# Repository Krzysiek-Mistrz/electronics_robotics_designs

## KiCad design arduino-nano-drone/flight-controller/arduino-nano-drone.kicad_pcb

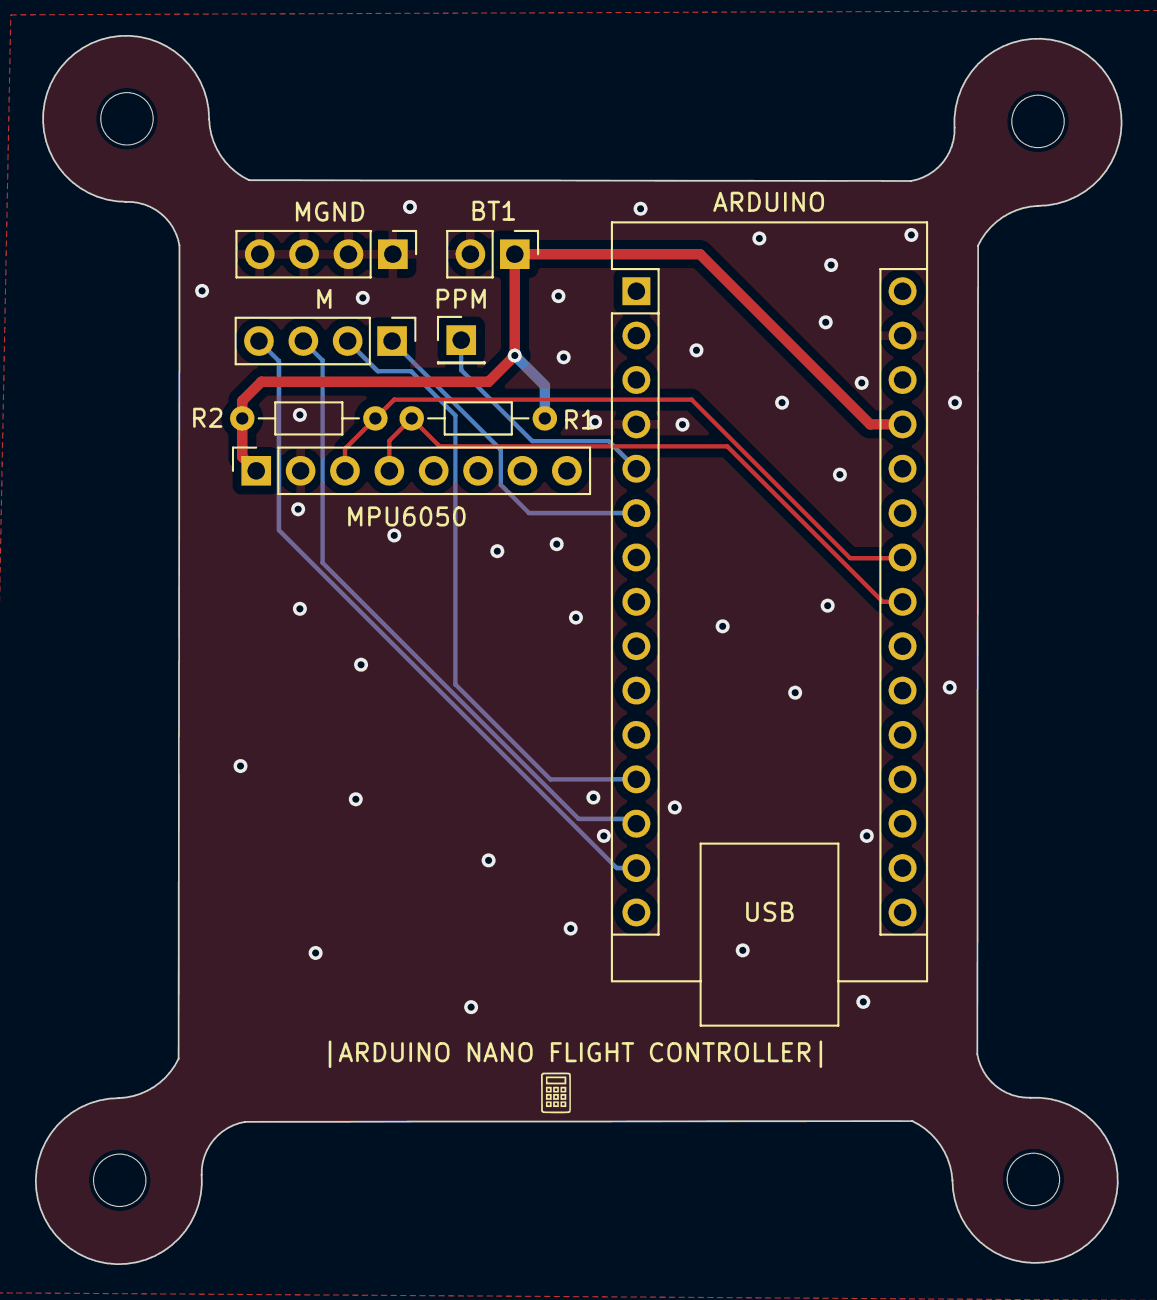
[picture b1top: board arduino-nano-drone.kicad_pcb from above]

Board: 2 copper layers, 62.2 x 70.3 mm, 8 parts (0 on the bottom side), 9 nets.

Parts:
ARDUINO: Arduino_Nano_v2.x; Arduino_Nano
BT1: Battery; PinHeader_1x02_P2.54mm_Vertical
M: Conn_01x04_Pin; PinHeader_1x04_P2.54mm_Vertical
MGND: motors pins; PinHeader_1x04_P2.54mm_Vertical
MPU6050: mpu6050 socket pins; PinSocket_1x08_P2.54mm_Vertical
PPM: Conn_01x01_Pin; PinHeader_1x01_P2.54mm_Vertical
R1, R2: 4.7k; R_Axial_DIN0204_L3.6mm_D1.6mm_P7.62mm_Horizontal

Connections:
/SCL: ARDUINO.24 (A5), MPU6050.3, R2.2
/SDA: ARDUINO.23 (A4), MPU6050.4, R1.2
GND: ARDUINO.4 (GND), ARDUINO.29 (GND), BT1.2 (-), MGND.1, MGND.2, MGND.3, MGND.4, MPU6050.2
unnamed: ARDUINO.5 (D2), PPM.1
unnamed: ARDUINO.6 (D3), M.1
unnamed: ARDUINO.12 (D9), M.2
unnamed: ARDUINO.13 (D10), M.3
unnamed: ARDUINO.14 (D11), M.4
VCC: ARDUINO.27 (+5V), BT1.1 (+), MPU6050.1, R1.1, R2.1

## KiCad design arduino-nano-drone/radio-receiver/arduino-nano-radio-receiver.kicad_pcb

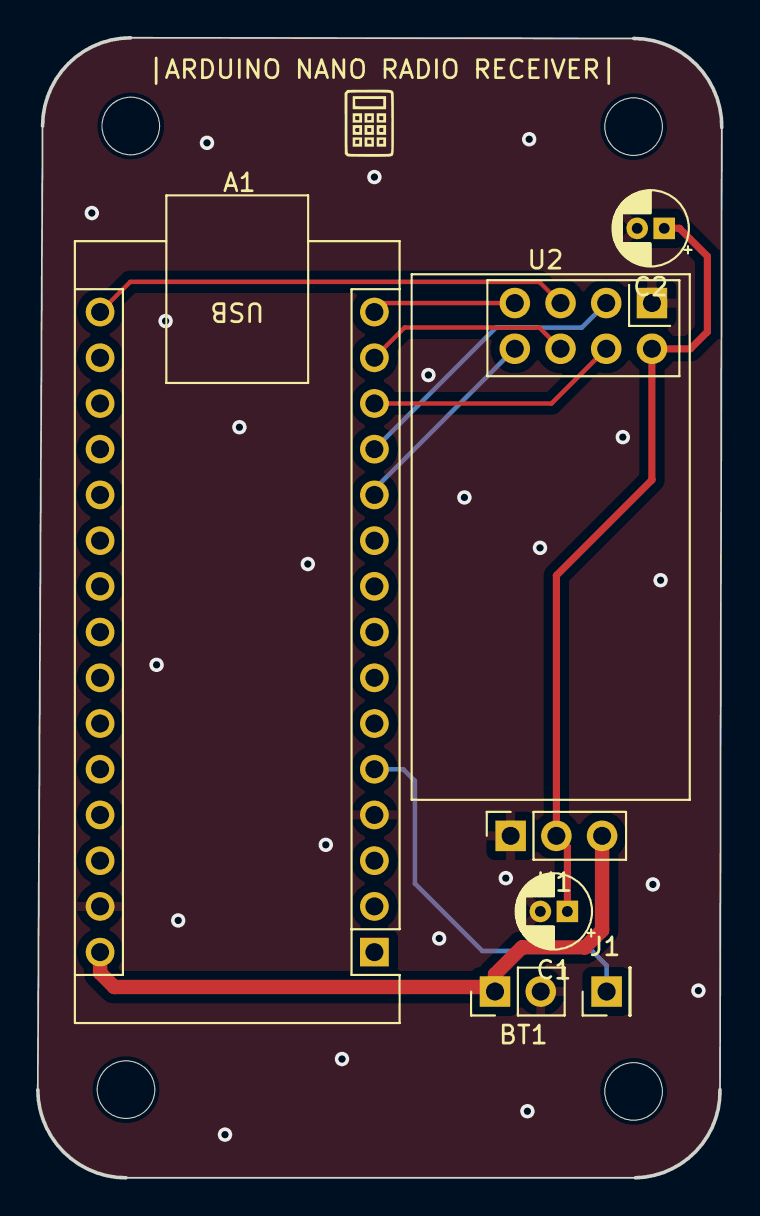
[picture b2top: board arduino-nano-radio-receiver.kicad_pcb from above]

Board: 2 copper layers, 38.0 x 63.3 mm, 7 parts (0 on the bottom side), 10 nets.

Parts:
A1: Arduino_Nano_v2.x; Arduino_Nano
BT1: Battery; PinHeader_1x02_P2.54mm_Vertical
C1, C2: 10u; CP_Radial_D4.0mm_P1.50mm
J1: Conn_01x01_Pin; PinHeader_1x01_P2.54mm_Vertical
U1: AMS1117-3.3; PinSocket_1x03_P2.54mm_Vertical
U2: NRF24L01_Breakout; nRF24L01_Breakout

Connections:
+3.3V: C1.1, C2.1, U1.2 (VO), U2.2 (VCC)
+12V: A1.30 (VIN), BT1.1 (+), U1.3 (VI)
/CE: A1.12 (D9), U2.3 (CE)
/CSN: A1.13 (D10), U2.4 (~CSN)
/IRQ: A1.11 (D8), U2.8 (IRQ)
/MISO: A1.15 (D12), U2.7 (MISO)
/MOSI: A1.14 (D11), U2.6 (MOSI)
/SCK: A1.16 (D13), U2.5 (SCK)
GND: A1.4 (GND), A1.29 (GND), BT1.2 (-), C1.2, C2.2, U1.1 (GND), U2.1 (GND)
unnamed: A1.5 (D2), J1.1

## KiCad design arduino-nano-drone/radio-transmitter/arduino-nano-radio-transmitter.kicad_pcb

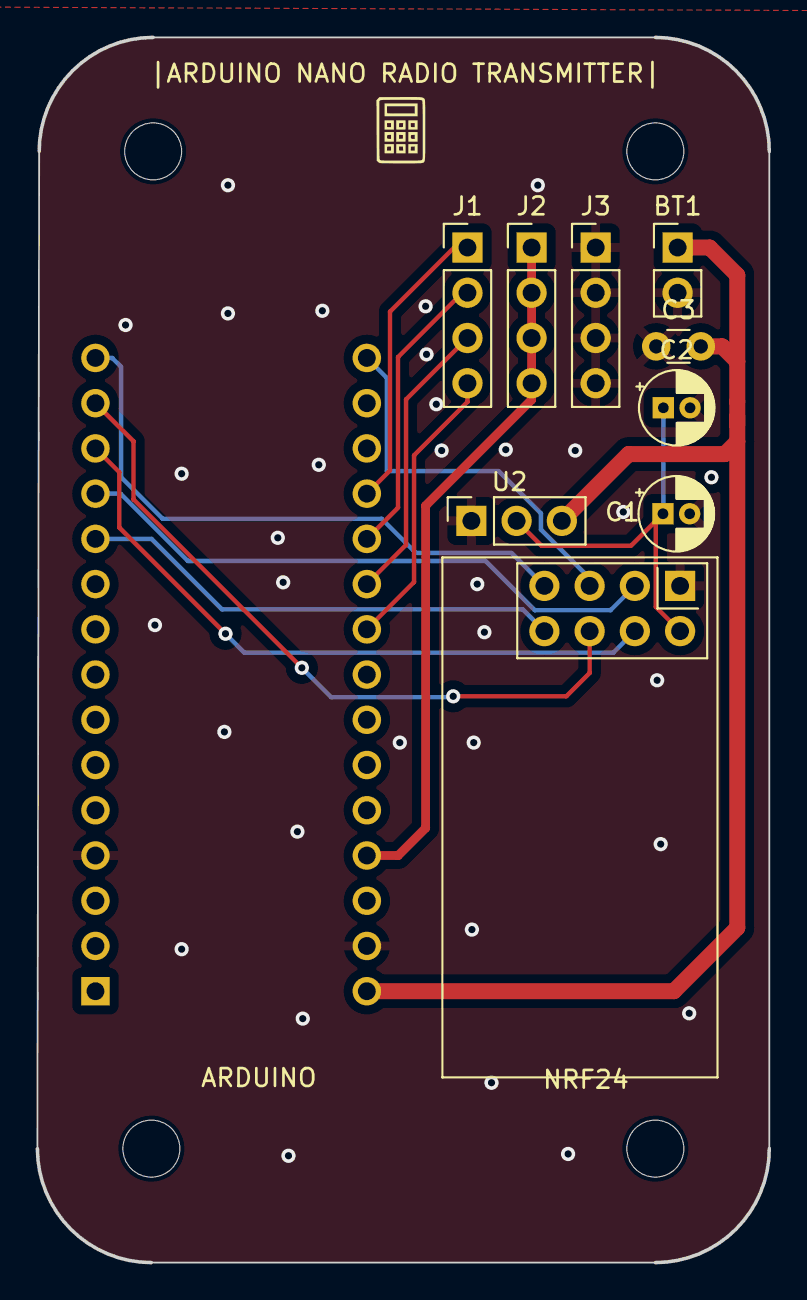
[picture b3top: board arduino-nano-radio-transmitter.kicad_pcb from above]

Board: 2 copper layers, 41.1 x 68.8 mm, 10 parts (1 on the bottom side), 14 nets.

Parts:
A1: Arduino_Nano_v2.x; Arduino_Nano
BT1: Battery; PinHeader_1x02_P2.54mm_Vertical
C1, C2: 10u; CP_Radial_D4.0mm_P1.50mm
C3: 100n; C_Disc_D3.0mm_W1.6mm_P2.50mm
J1, J2, J3: Conn_01x04_Pin; PinHeader_1x04_P2.54mm_Vertical
U2: AMS1117-3.3; PinSocket_1x03_P2.54mm_Vertical
U3: NRF24L01_Breakout; nRF24L01_Breakout

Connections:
+3.3V: C1.1, C2.1, U2.2 (VO), U3.2 (VCC)
+12V: A1.30 (VIN), BT1.1 (+), C3.2, U2.3 (VI)
/CE: A1.12 (D9), U3.3 (CE)
/CSN: A1.13 (D10), U3.4 (~CSN)
/IRQ: A1.11 (D8), U3.8 (IRQ)
/MISO: A1.15 (D12), U3.7 (MISO)
/MOSI: A1.14 (D11), U3.6 (MOSI)
/SCK: A1.16 (D13), U3.5 (SCK)
GND: A1.4 (GND), A1.29 (GND), BT1.2 (-), C1.2, C2.2, C3.1, J3.1, J3.2, J3.3, J3.4, U2.1 (GND), U3.1 (GND)
unnamed: A1.27 (+5V), J2.1, J2.2, J2.3, J2.4
unnamed: A1.19 (A0), J1.1
unnamed: A1.20 (A1), J1.2
unnamed: A1.21 (A2), J1.3
unnamed: A1.22 (A3), J1.4

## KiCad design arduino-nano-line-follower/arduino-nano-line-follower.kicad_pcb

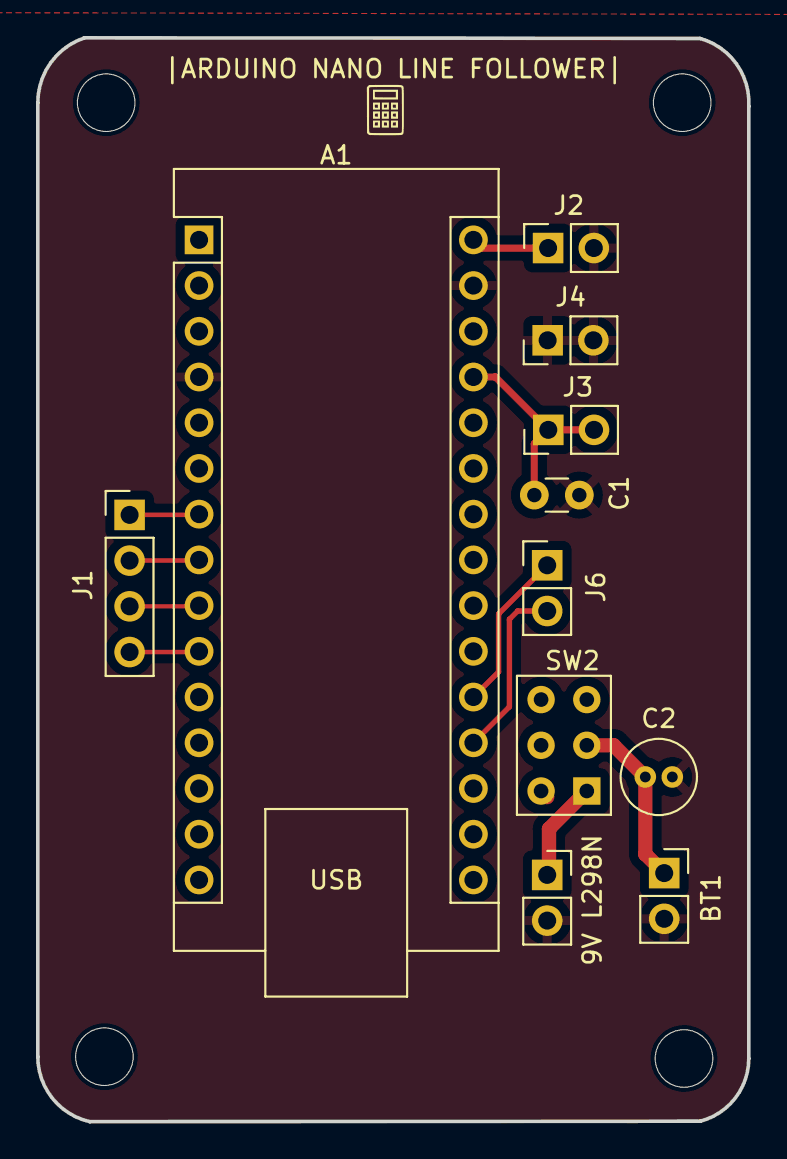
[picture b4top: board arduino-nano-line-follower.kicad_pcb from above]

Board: 2 copper layers, 39.5 x 60.2 mm, 11 parts (0 on the bottom side), 11 nets.

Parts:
9V L298N: 9v_gnd_l293d; PinSocket_1x02_P2.54mm_Vertical
A1: Arduino_Nano_Every; Arduino_Nano
BT1: Battery; PinSocket_1x02_P2.54mm_Vertical
C1: 100n; C_Disc_D3.0mm_W1.6mm_P2.50mm
C2: 10u; C_Radial_D4.0mm_H5.0mm_P1.50mm
J1: l298_input_pins; PinHeader_1x04_P2.54mm_Vertical
J2: arduino_vcc_gnd; PinSocket_1x02_P2.54mm_Vertical
J3: 5v_ir_sensors_pins; PinHeader_1x02_P2.54mm_Vertical
J4: gnd_ir_sensors_pins; PinHeader_1x02_P2.54mm_Vertical
J6: ir_signal; PinHeader_1x02_P2.54mm_Vertical
SW2: pwr_switch; SW_NKK_G1xJP

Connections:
+5V: A1.30 (VIN), J2.1
+9V: BT1.1 (+), C2.1, SW2.2
GND: 9V L298N.2, A1.4 (GND), A1.29 (GND), BT1.2 (-), C1.2, C2.2, J2.2, J4.1, J4.2
unnamed: A1.27 (+5V), C1.1, J3.1, J3.2
unnamed: A1.19 (A0), J6.2
unnamed: A1.20 (A1), J6.1
unnamed: A1.7 (D4), J1.1
unnamed: A1.8 (D5), J1.2
unnamed: A1.9 (D6), J1.3
unnamed: A1.10 (D7), J1.4
unnamed: 9V L298N.1, SW2.1

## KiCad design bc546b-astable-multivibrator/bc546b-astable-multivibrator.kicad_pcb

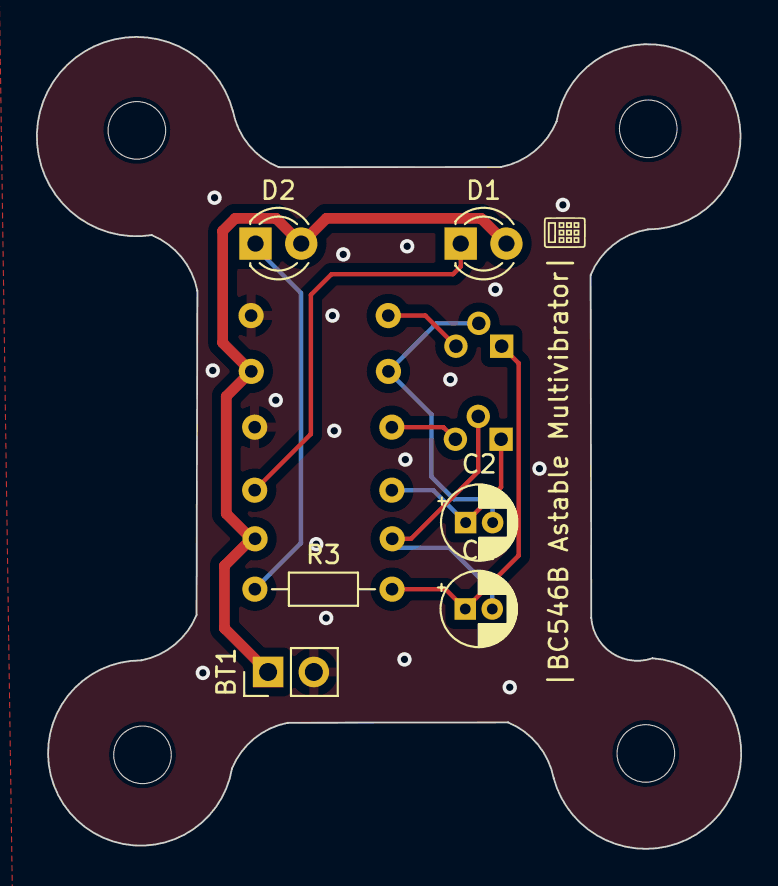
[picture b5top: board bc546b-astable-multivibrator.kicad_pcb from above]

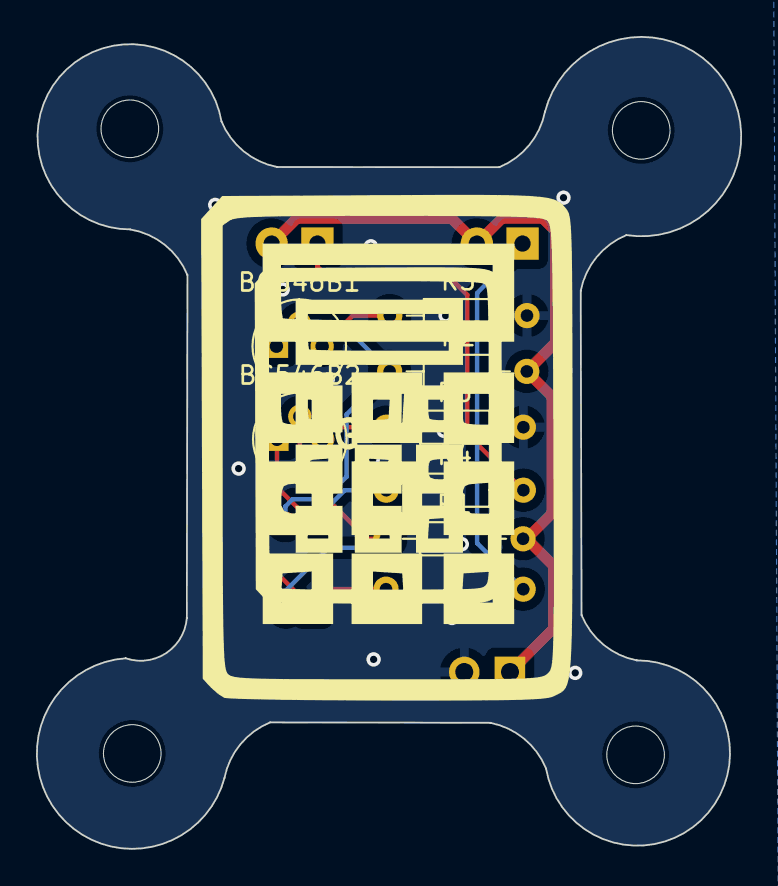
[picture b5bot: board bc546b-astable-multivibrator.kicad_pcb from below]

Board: 2 copper layers, 39.1 x 45.1 mm, 13 parts (7 on the bottom side), 10 nets.

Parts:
BC546B1, BC546B2: NPN; TO-92
BT1: Battery; PinHeader_1x02_P2.54mm_Vertical
C1, C2: 10u; CP_Radial_D4.0mm_P1.50mm
D1, D2: LED; LED_D3.0mm
R1, R2: 100k; R_Axial_DIN0204_L3.6mm_D1.6mm_P7.62mm_Horizontal
R3, R4: 560; R_Axial_DIN0204_L3.6mm_D1.6mm_P7.62mm_Horizontal
R5, R6: 100; R_Axial_DIN0204_L3.6mm_D1.6mm_P7.62mm_Horizontal

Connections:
+9V: BT1.1 (+), D1.2 (A), D2.2 (A), R1.2, R2.2
/I1: BC546B2.2 (B), C1.2, R1.1
/I2: BC546B1.2 (B), C2.2, R2.1
GND: BT1.2 (-), R5.2, R6.2
unnamed: BC546B1.1 (C), C1.1, R3.2
unnamed: BC546B1.3 (E), R5.1
unnamed: BC546B2.1 (C), C2.1, R4.1
unnamed: BC546B2.3 (E), R6.1
unnamed: D1.1 (K), R4.2
unnamed: D2.1 (K), R3.1

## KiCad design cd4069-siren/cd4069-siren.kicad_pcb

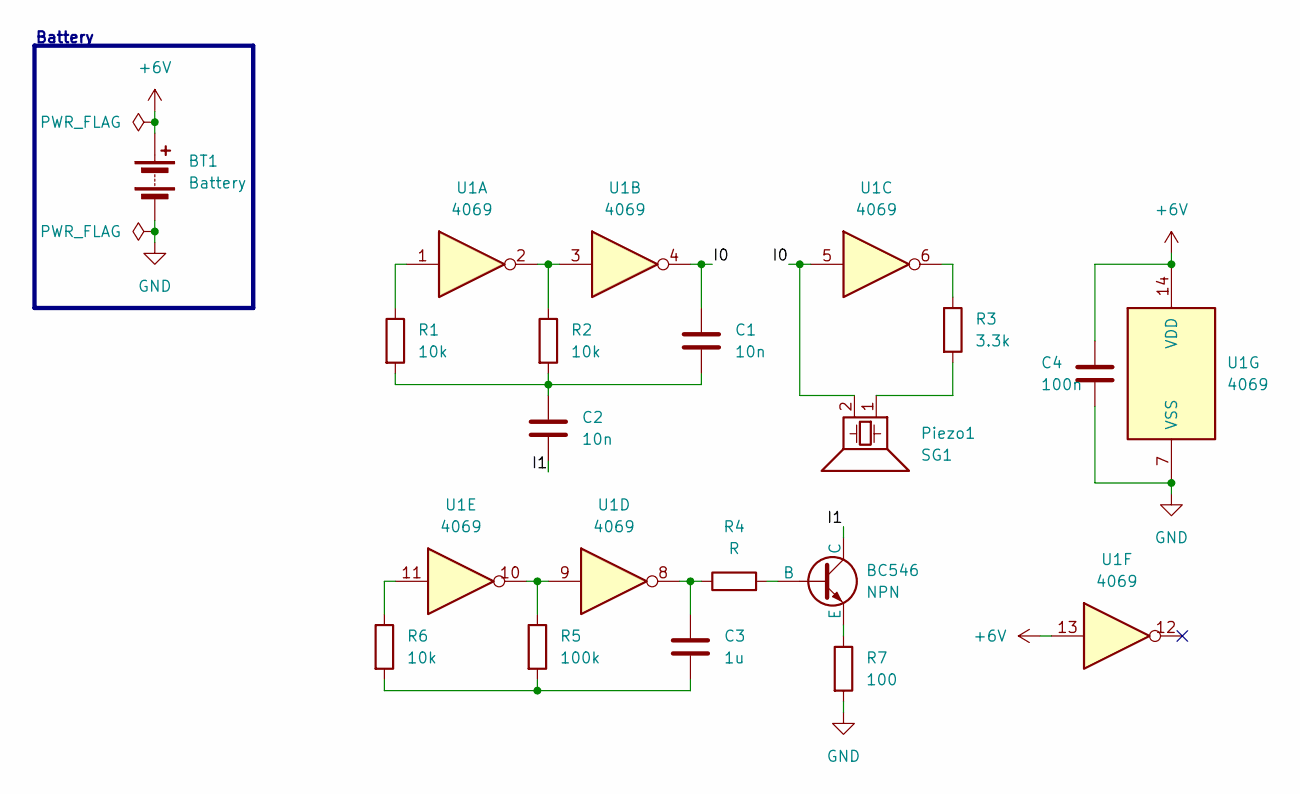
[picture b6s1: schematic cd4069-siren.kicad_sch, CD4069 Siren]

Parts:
BC546: NPN; TO-92
BT1: Battery; PinHeader_1x02_P2.54mm_Vertical
C1, C2: 10n; C_Disc_D3.0mm_W1.6mm_P2.50mm
C3: 1u; C_Disc_D3.0mm_W1.6mm_P2.50mm
C4: 100n; C_Disc_D3.0mm_W1.6mm_P2.50mm
Piezo1: SG1; Buzzer_12x9.5RM7.6
R1, R2, R6: 10k; R_Axial_DIN0204_L3.6mm_D1.6mm_P7.62mm_Horizontal
R3: 3.3k; R_Axial_DIN0204_L3.6mm_D1.6mm_P7.62mm_Horizontal
R4: R; R_Axial_DIN0204_L3.6mm_D1.6mm_P7.62mm_Horizontal
R5: 100k; R_Axial_DIN0204_L3.6mm_D1.6mm_P7.62mm_Horizontal
R7: 100; R_Axial_DIN0204_L3.6mm_D1.6mm_P7.62mm_Horizontal
U1: 4069; DIP-14_W7.62mm

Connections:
+6V: BT1.1 (+), C4.1, U1.13, U1.14 (VDD); also elsewhere on the board
/I0: C1.1, Piezo1.2, U1.4, U1.5; also elsewhere on the board
/I1: BC546.1 (C), C2.2
GND: BT1.2 (-), C4.2, R7.2, U1.7 (VSS); also elsewhere on the board
unnamed: BC546.2 (B), R4.2
unnamed: BC546.3 (E), R7.1
unnamed: C1.2, C2.1, R1.2, R2.2
unnamed 7: C3.1, R4.1, U1.8; also elsewhere on the board
unnamed: C3.2, R5.2, R6.2
unnamed: Piezo1.1, R3.2
unnamed 10: R1.1, U1.1; also elsewhere on the board
unnamed 11: R2.1, U1.2, U1.3; also elsewhere on the board
unnamed 12: R3.1, U1.6; also elsewhere on the board
unnamed 13: R5.1, U1.9, U1.10; also elsewhere on the board
unnamed 14: R6.1, U1.11; also elsewhere on the board

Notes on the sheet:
Battery

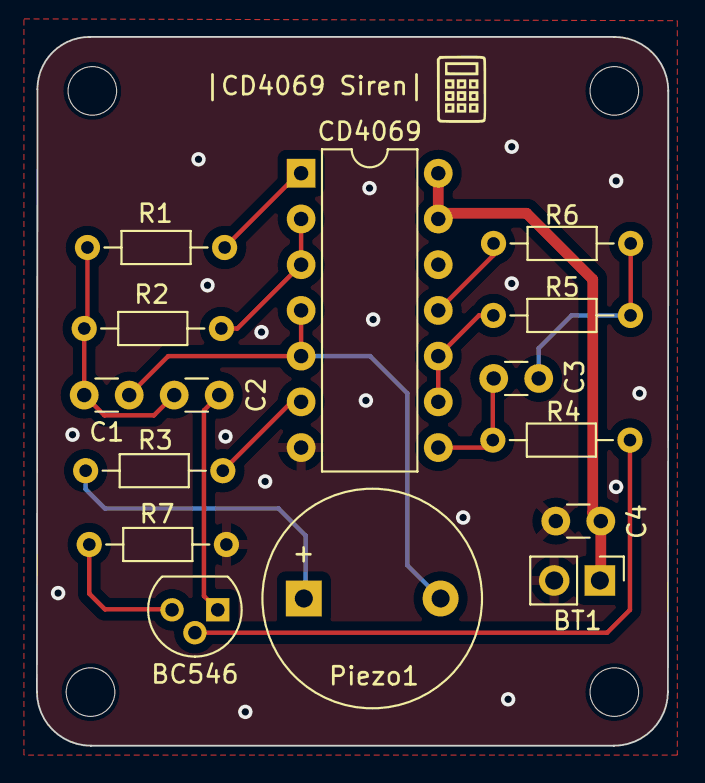
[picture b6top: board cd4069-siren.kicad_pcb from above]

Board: 2 copper layers, 35.1 x 39.4 mm, 15 parts (0 on the bottom side), 15 nets.

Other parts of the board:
CD4069: 4069; DIP-14_W7.62mm

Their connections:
+6V: CD4069.13, CD4069.14 (VDD); also elsewhere on the board
/I0: CD4069.4, CD4069.5; also elsewhere on the board
GND: CD4069.7 (VSS); also elsewhere on the board
unnamed 7: CD4069.8; also elsewhere on the board
unnamed 10: CD4069.1; also elsewhere on the board
unnamed 11: CD4069.2, CD4069.3; also elsewhere on the board
unnamed 12: CD4069.6; also elsewhere on the board
unnamed 13: CD4069.9, CD4069.10; also elsewhere on the board
unnamed 14: CD4069.11; also elsewhere on the board
